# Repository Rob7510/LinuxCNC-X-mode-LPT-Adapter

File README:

# LinuxCNC signal adapter for a parallel port operating in X-mode.
**Version 153-01C**  work in progress

Many PC printer port cards can be operated in 'X' mode in **LinuxCNC**.
In X-mode the card provides 9 input ports (Pin 1, Pin 10-17) and 8 output ports (Pin 2 - Pin 9). This is usually sufficient for a small CNC. I do not know if other software than LinuxCNC can set a Printer port card in X-mode.

I do not know a commercial version of an X-mode LPT breakout board, but they are easy to build using a commercially produced dual layer PCB. This is the X-mode adapter design that I use for my CNC's running LinuxCNC.
The hardware is designed in Eagle; the .sch and .brd files are included, as well
as the Gerber files for manufacturing. The board size is kept to 10 x 10 cm to keep the manufacturing costs low (with Far-East PCB services).
The **CERN-OHL-P V2** license applies, which means that you are free to copy the design, modify it and
sell the result.

**Design features:**

  * The breakout board Input and Output ports are electrically separated from the PC using fast optical couplers. The PC side of the circuit is powered via a small 5V DC/DC converter.
  * The board can be directly plugged into the PC printer connector, or connected via a standard 26 wire ribbon cable with a printer connector on the other end. The 26 pin connector can also be used to plug in a signal monitor.
  * The Inputs for Pins 10 through 17 support a wide range of input signals (<u>+</u> 30V). The Pin 1 Input is fully isolated from the whole adapter, and can handle up to 300V AC or DC, for instance to check presence of the mains or driver voltage.

**Inputs:**

**Pin 1** requires one or two series resistors (for DC) or capacitors (for AC) so that the effctive current through the bipolar optocoupler (PC814) is 4 - 6 mA:

* For standard 5V signals user 680 Ohm series resistance. For voltages over 100V use two components in series.
* For DC voltages make sure the power dissipation in the resistor(s) does not exceed their rating.
* For mains voltage use 2 x xxxnF for 127V and 2 x xxxnF for 230V. Each capacitor should preferably be rated for 400V.
* The P1 LED lights up when it detects the incoming signal.

**Pins 10 - 17** are set to about 0V (False) for an input between -30 and + 0.5 V, and to 5V (True) for an input between 1.5 an 30V. The input lines are filtered to suppress high frequency (~ 10 KHz) pulses. The 10 pin ribbon connector is an alternative input for Pin 10 - 17, and provides ground and 5V to supply a remote input panel.

**Outputs:**

**Pins 2 - 9 **drive 5V signals with a current up to 10 mA. The 10 pin ribbon connector is an alternative output, and provides ground and 5V to supply remote distribution panels.

**Power supply:** To be updated

**Software:** To be updated

**Assembly:**

The X-mode adapter 153-01C is designed with through hole components to facilitate home assembly. The component list (BOM) gives the details.
The small capacitors (with values between 10 and 100 nF) are required to suppress RF disturbance.
The antiparallel diode next to the power connector will prevent damage in case the 5V is connected with the wrong polarity.
Is no electric separation from the PC is required, the 5V DC/DC converter can be replaced by two wires, and a USB power cable can be connected to a USB port on the PC.

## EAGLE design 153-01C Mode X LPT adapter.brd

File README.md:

# LinuxCNC signal adapter for a parallel port operating in X-mode.
**Version 153-01C**

Many PC printer port option boards can be operated in 'X' mode in **LinuxCNC**, by setting this mode in the 'loadrt hal_parport' command.
In X-mode the 25-pin I/O connector provides 9 input ports (Pin 1, Pin 10-17) and 8 output ports (Pin 2 - Pin 9). This is usually sufficient for a small CNC. (I do not know if other software than LinuxCNC can set a Printer port card in X-mode).

The signal breakout for an X-mode adapter can be home built with a low cost dual layer PCB, with full electric isolation from the connected PC. This document provides the Eagle design and the Gerber manufacturing files for such a Breakout Board (BoB). The board size is kept to 10 x 10 cm to keep the manufacturing costs low (with Far-East PCB services). The **CERN-OHL-P V2** OpenHardware license applies, hence you are free to copy the design, modify it and sell/use the result.

**Design:**

  * The BoB input and output ports are electrically separated from the PC using optical couplers. The PC side of the circuit is powered via a small 5V isolated DC/DC converter. Te board uses approximately 150 mA, and can be powered with an old USB-A power adapter.
  * The board can be directly plugged into a 25 pin PC printer port, or connected via a standard 26 wire ribbon cable with a printer port connector on the other end. The 26 pin connector can also be used to plug in a signal monitor.
  * The Inputs for Pins 10 through 17 support a wide range of input signals (<u>+</u> 30V). The Pin 1 Input is fully isolated from the whole board, and can handle up to 300V AC or DC signals, for instance to check presence of the mains voltage or Power supply output.

**Inputs:**

**Pin 1** requires one or two series resistors (for DC) or capacitors (for AC) so that the current through the bipolar optocoupler (PC814) is in the range of 4 - 10 mA:
* For standard 5V signals use a 680 Ohm resistor. For voltages over 100V use two components in series.
* For DC voltages make sure the power dissipation in the resistor(s) does not exceed their rating.
* For 230V mains voltage use 2 x 150nF (400V) in series. To keep high voltages away from the board, mount the capacitors or resistors at the source, and fill the two onboard slots with jumpers.
* The P1 LED lights up when it detects a valid signal.

**Pins 10 - 17** are set to about 0V (False) for an input between -30 and + 0.5 V, and to 5V (True) for an input between 1.5 an 30V. These inputs suppress high frequency (>5KHz) pulses. The 10 pin ribbon connector connects Pin 10 - 17, as well as GND and 5V to a remote input panel.

**Outputs:**

**Pins 2 - 9 ** drive 5V signals with a current up to 35 mA. The fast optical couplers (6N137) can handle pulses as short as 2 microseconds. The 10 pin ribbon connector is for connection to a remote breakout panel. All outputs (typically used for stepper signals) can be collectively turned off with a logic input signal.

**Power supply:**

The USB connector on the BoB should be connected to an separate 5V USB power supply to maintain electric isolation from the PC. The onboard 2-pin 5V connector can be used to supply other 5V hardware like relay boards. If PC isolation is not needed, the BoB can be connected to one of the PC USB plugs, and the DC/DC converter can be replaced by two wires.

**Software:** XPtest-0.hal and xptest-0.xml provide a display of the X-mode adapter I/O ports and check / set their status. The test assumes that the BoB connects to the first printer port that the PC discovers.

**Assembly:**

The X-mode adapter 153-01C uses through-hole components to facilitate home assembly. The component list (BOM) has the details.
The small capacitors (useful values between 10 and 100 nF) are required to suppress RF disturbance.
The antiparallel diode next to the power connector will prevent damage in case the 5V is connected with the wrong polarity (I hate replacing dead chips).

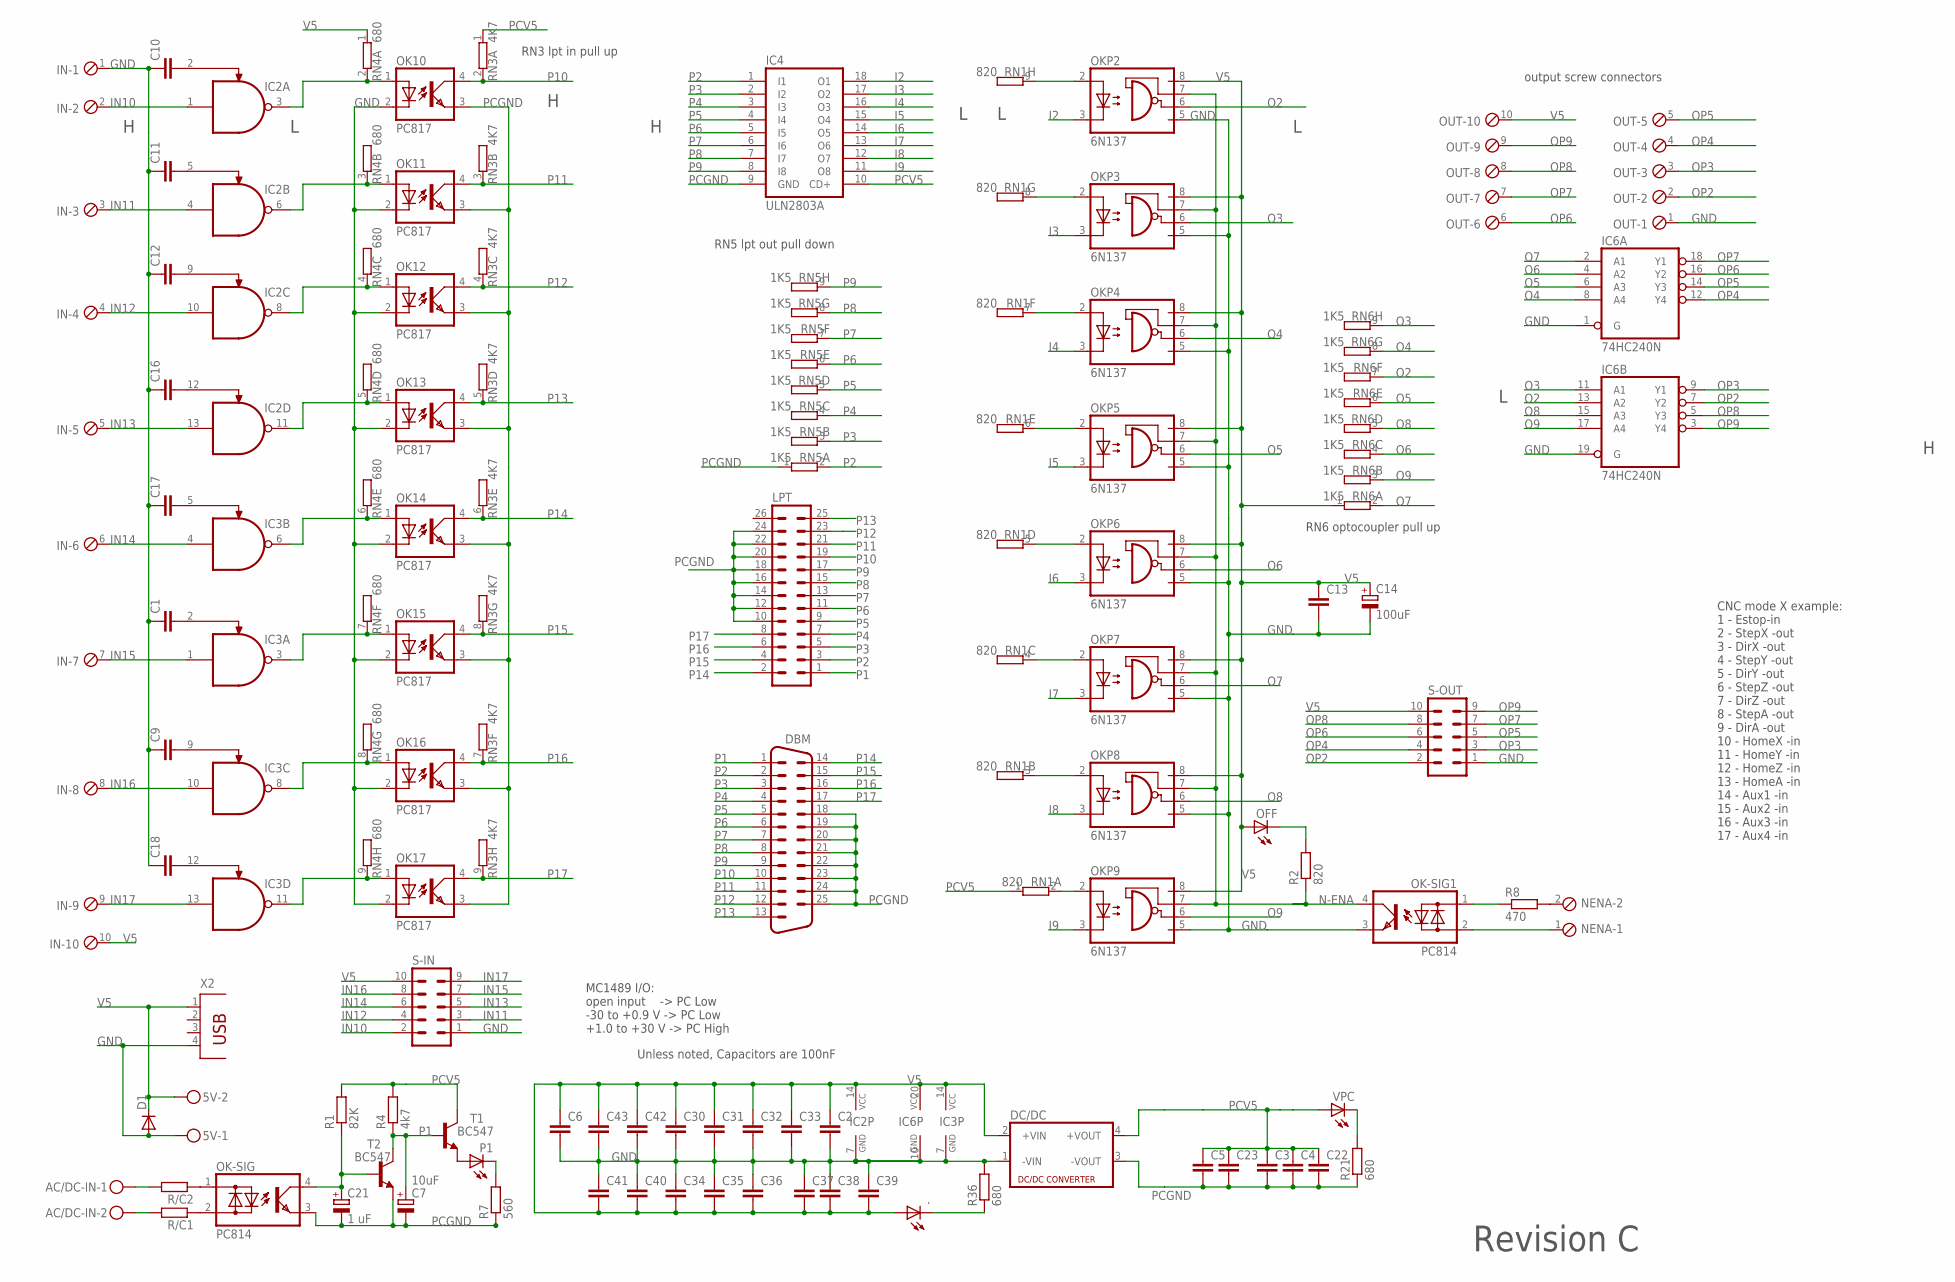
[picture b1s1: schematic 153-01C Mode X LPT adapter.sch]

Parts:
5V: MKDSN1,5/2-5,08
.: LED3MM
AC/DC-IN: MKDSN1,5/2-5,08
C1, C2, C3, C4, C5, C6, C9, C10, C11, C12, C13, C16, C17, C18, C22, C23, C30, C31, C32, C33, C34, C35, C36, C37, C38, C39, C40, C41, C42, C43: C-EU025-024X044; C025-024X044
C7: 10uF; E5-6
C14: 100uF; E3,5-8
C21: 1 uF; E2,5-6
D1: 1N4148DO35-10; DO35-10
DBM: M25HP
DC/DC: VA-1205S; 4SIL
IC2, IC3: MC1489DIP; DIL14
IC4: ULN2803A; DIL18
IC6: 74HC240N; DIL20
IN: MPT10; 10POL254
LPT: ML26
NENA: MPT2; 2POL254
OFF: LED3MM
OK10, OK11, OK12, OK13, OK14, OK15, OK16, OK17: PC817; DIL04
OK-SIG, OK-SIG1: PC814; DIL04
OKP2, OKP3, OKP4, OKP5, OKP6, OKP7, OKP8, OKP9: 6N137; DIL08
OUT: MPT10; 10POL254
P1: LED3MM
R1: 82K; 0207/10
R2: 820; 0207/10
R4: 4k7; 0207/10
R7: 560; 0207/10
R8: 470; 0207/10
R21, R36: 680; 0207/10
R/C1, R/C2: R-EU_0309/10; 0309/10
RN1: 820; SIL9
RN3: 4K7; SIL9
RN4: 680; SIL9
RN5, RN6: 1K5; SIL9
S-IN: ML10
S-OUT: ML10
T1, T2: BC547; TO92
VPC: LED3MM
X2: PN87520

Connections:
GND: 5V.1, C1.1, C2.2, C6.2, C9.1, C10.1, C11.1, C12.1, C13.2, C14.-, C16.1, C17.1, C18.1, C30.2, C31.2, C32.2, C33.2, C34.1, C35.1, C36.1, C37.1, C38.1, C39.1, C40.1, C41.1, C42.2, C43.2, D1.A, DC/DC.1 (-VIN), IC2.7 (GND), IC3.7 (GND), IC6.1 (G), IC6.10 (GND), IC6.19 (G), IN.1, OK10.2 (C), OK11.2 (C), OK12.2 (C), OK13.2 (C), OK14.2 (C), OK15.2 (C), OK16.2 (C), OK17.2 (C), OK-SIG1.3 (E), OKP2.5 (GND), OKP3.5 (GND), OKP4.5 (GND), OKP5.5 (GND), OKP6.5 (GND), OKP7.5 (GND), OKP8.5 (GND), OKP9.5 (GND), OUT.1, R36.2, S-IN.1, S-OUT.1, X2.4
I2: IC4.18 (O1), OKP2.3 (C)
I3: IC4.17 (O2), OKP3.3 (C)
I4: IC4.16 (O3), OKP4.3 (C)
I5: IC4.15 (O4), OKP5.3 (C)
I6: IC4.14 (O5), OKP6.3 (C)
I7: IC4.13 (O6), OKP7.3 (C)
I8: IC4.12 (O7), OKP8.3 (C)
I9: IC4.11 (O8), OKP9.3 (C)
IN10: IC2.1 (I0), IN.2, S-IN.2
IN11: IC2.4 (I0), IN.3, S-IN.3
IN12: IC2.10 (I0), IN.4, S-IN.4
IN13: IC2.13 (I0), IN.5, S-IN.5
IN14: IC3.4 (I0), IN.6, S-IN.6
IN15: IC3.1 (I0), IN.7, S-IN.7
IN16: IC3.10 (I0), IN.8, S-IN.8
IN17: IC3.13 (I0), IN.9, S-IN.9
unnamed: OKP6.2 (A), RN1.5 (2)
unnamed: OKP9.2 (A), RN1.2
unnamed: C10.2, IC2.2 (I1)
unnamed: R21.2, VPC.K (C)
unnamed: C17.2, IC3.5 (I1)
unnamed: OFF.K (C), R2.2
unnamed: IC2.6 (O), OK11.1 (A), RN4.3 (2)
unnamed: IC2.8 (O), OK12.1 (A), RN4.4 (2)
unnamed: C1.2, IC3.2 (I1)
unnamed: C9.2, IC3.9 (I1)
unnamed: C18.2, IC3.12 (I1)
unnamed: IC2.3 (O), OK10.1 (A), RN4.2
unnamed: IC2.11 (O), OK13.1 (A), RN4.5 (2)
unnamed: IC3.6 (O), OK14.1 (A), RN4.6 (2)
unnamed: IC3.3 (O), OK15.1 (A), RN4.7 (2)
unnamed: IC3.8 (O), OK16.1 (A), RN4.8 (2)
unnamed: OK-SIG.1 (AC1), R/C2.1
unnamed: OK-SIG.2 (AC2), R/C1.1
unnamed: IC3.11 (O), OK17.1 (A), RN4.9 (2)
unnamed: AC/DC-IN.2, R/C1.2
unnamed: AC/DC-IN.1, R/C2.2
unnamed: OKP7.2 (A), RN1.4 (2)
unnamed: OKP8.2 (A), RN1.3 (2)
unnamed: C21.+, OK-SIG.4 (C), R1.1, T2.2 (B)
unnamed: ..K (C), R36.1
unnamed: C11.2, IC2.5 (I1)
unnamed: C12.2, IC2.9 (I1)
unnamed: C16.2, IC2.12 (I1)
unnamed: OKP5.2 (A), RN1.6 (2)
unnamed: OKP4.2 (A), RN1.7 (2)
unnamed: OK-SIG1.1 (AC1), R8.1
unnamed: OKP3.2 (A), RN1.8 (2)
unnamed: OKP2.2 (A), RN1.9 (2)
unnamed: P1.K (C), R7.2
unnamed: P1.A, T1.1 (E)
unnamed: NENA.2, R8.2
unnamed: NENA.1, OK-SIG1.2 (AC2)
N-ENA: OK-SIG1.4 (C), OKP2.7 (VE), OKP3.7 (VE), OKP4.7 (VE), OKP5.7 (VE), OKP6.7 (VE), OKP7.7 (VE), OKP8.7 (VE), OKP9.7 (VE), R2.1
O2: IC6.13 (A2), OKP2.6 (VO), RN6.7 (2)
O3: IC6.11 (A1), OKP3.6 (VO), RN6.9 (2)
O4: IC6.8 (A4), OKP4.6 (VO), RN6.8 (2)
O5: IC6.6 (A3), OKP5.6 (VO), RN6.6 (2)
O6: IC6.4 (A2), OKP6.6 (VO), RN6.4 (2)
O7: IC6.2 (A1), OKP7.6 (VO), RN6.2
O8: IC6.15 (A3), OKP8.6 (VO), RN6.5 (2)
O9: IC6.17 (A4), OKP9.6 (VO), RN6.3 (2)
OP2: IC6.7 (Y2), OUT.2, S-OUT.2
OP3: IC6.9 (Y1), OUT.3, S-OUT.3
OP4: IC6.12 (Y4), OUT.4, S-OUT.4
OP5: IC6.14 (Y3), OUT.5, S-OUT.5
OP6: IC6.16 (Y2), OUT.6, S-OUT.6
OP7: IC6.18 (Y1), OUT.7, S-OUT.7
OP8: IC6.5 (Y3), OUT.8, S-OUT.8
OP9: IC6.3 (Y4), OUT.9, S-OUT.9
P1: C7.+, DBM.1, LPT.1, R4.1, T1.2 (B), T2.3 (C)
P2: DBM.2, IC4.1 (I1), LPT.3, RN5.2
P3: DBM.3, IC4.2 (I2), LPT.5, RN5.3 (2)
P4: DBM.4, IC4.3 (I3), LPT.7, RN5.4 (2)
P5: DBM.5, IC4.4 (I4), LPT.9, RN5.5 (2)
P6: DBM.6, IC4.5 (I5), LPT.11, RN5.6 (2)
P7: DBM.7, IC4.6 (I6), LPT.13, RN5.7 (2)
P8: DBM.8, IC4.7 (I7), LPT.15, RN5.8 (2)
P9: DBM.9, IC4.8 (I8), LPT.17, RN5.9 (2)
P10: DBM.10, LPT.19, OK10.4 (COL), RN3.2
P11: DBM.11, LPT.21, OK11.4 (COL), RN3.3 (2)
P12: DBM.12, LPT.23, OK12.4 (COL), RN3.4 (2)
P13: DBM.13, LPT.25, OK13.4 (COL), RN3.5 (2)
P14: DBM.14, LPT.2, OK14.4 (COL), RN3.6 (2)
P15: DBM.15, LPT.4, OK15.4 (COL), RN3.8 (2)
P16: DBM.16, LPT.6, OK16.4 (COL), RN3.7 (2)
P17: DBM.17, LPT.8, OK17.4 (COL), RN3.9 (2)
PCGND: C3.2, C4.2, C5.2, C7.-, C21.-, C22.2, C23.2, DBM.18, DBM.19, DBM.20, DBM.21, DBM.22, DBM.23, DBM.24, DBM.25, DC/DC.3 (-VOUT), IC4.9 (GND), LPT.10, LPT.12, LPT.14, LPT.16, LPT.18, LPT.20, LPT.22, LPT.24, OK10.3 (EMIT), OK11.3 (EMIT), OK12.3 (EMIT), OK13.3 (EMIT), OK14.3 (EMIT), OK15.3 (EMIT), OK16.3 (EMIT), OK17.3 (EMIT), OK-SIG.3 (E), R7.1, R21.1, RN5.1, T2.1 (E)
PCV5: C3.1, C4.1, C5.1, C22.1, C23.1, DC/DC.4 (+VOUT), IC4.10 (CD+), R1.2, R4.2, RN1.1, RN3.1, T1.3 (C), VPC.A
V5: 5V.2, ..A, C2.1, C6.1, C13.1, C14.+, C30.1, C31.1, C32.1, C33.1, C34.2, C35.2, C36.2, C37.2, C38.2, C39.2, C40.2, C41.2, C42.1, C43.1, D1.C, DC/DC.2 (+VIN), IC2.14 (VCC), IC3.14 (VCC), IC6.20 (VCC), IN.10, OFF.A, OKP2.8 (VCC), OKP3.8 (VCC), OKP4.8 (VCC), OKP5.8 (VCC), OKP6.8 (VCC), OKP7.8 (VCC), OKP8.8 (VCC), OKP9.8 (VCC), OUT.10, RN4.1, RN6.1, S-IN.10, S-OUT.10, X2.1

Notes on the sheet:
CNC mode X example: 1 - Estop-in 2 - StepX -out 3 - DirX -out 4 - StepY -out 5 - DirY -out 6 - StepZ -out 7 - DirZ -out 8 - StepA -out 9 - DirA -out 10 - HomeX -in 11 - HomeY -in 12 - HomeZ -in 13 - HomeA -in 14 - Aux1 -in 15 - Aux2 -in 16 - Aux3 -in 17 - Aux4 -in
MC1489 I/O: open input -> PC Low -30 to +0.9 V -> PC Low +1.0 to +30 V -> PC High
RN5 lpt out pull down
RN3 lpt in pull up
RN6 optocoupler pull up
output screw connectors
Unless noted, Capacitors are 100nF
Revision C

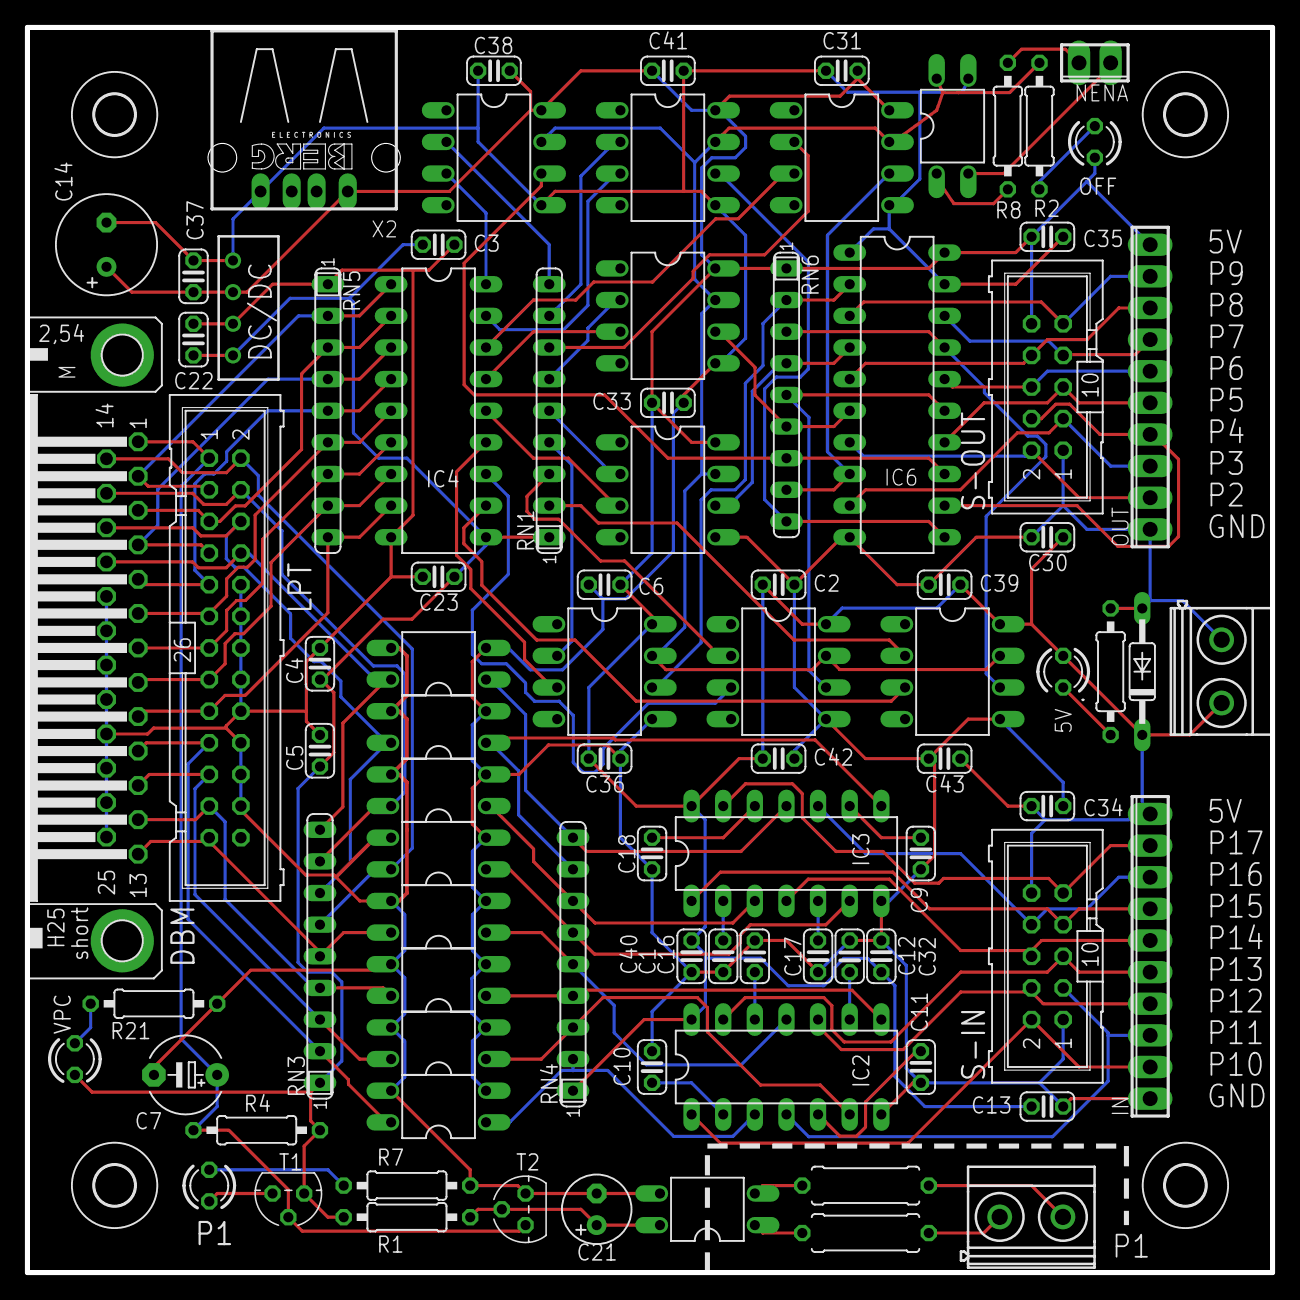
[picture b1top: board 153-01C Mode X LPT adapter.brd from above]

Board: 2 copper layers, 100.0 x 100.0 mm, 91 parts (0 on the bottom side), 91 nets.

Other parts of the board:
U$1, U$2, U$3, U$4: 3,2

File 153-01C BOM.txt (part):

Stückliste exportiert aus /home/robert/Project_data/Projects/153 LinuxCNC adapters/153-01C Mode X LPT adapter.sch am 03/07/2024 21:08

Part     Value     Device          Package         Description                           MF MPN          OC_FARNELL OC_NEWARK
.                  LED3MM          LED3MM          LED                                                                       
5V                 MKDSN1,5/2-5,08 MKDSN1,5/2-5,08 MKDSN 1,5/ 2-5,08 Printklemme                                             
AC/DC-IN           MKDSN1,5/2-5,08 MKDSN1,5/2-5,08 MKDSN 1,5/ 2-5,08 Printklemme                                             
C1                 C-EU025-024X044 C025-024X044    CAPACITOR, European symbol                                                
C2                 C-EU025-024X044 C025-024X044    CAPACITOR, European symbol                                                
C3                 C-EU025-024X044 C025-024X044    CAPACITOR, European symbol                                                
C4                 C-EU025-024X044 C025-024X044    CAPACITOR, European symbol                                                
C5                 C-EU025-024X044 C025-024X044    CAPACITOR, European symbol                                                
C6                 C-EU025-024X044 C025-024X044    CAPACITOR, European symbol                                                
C7       10uF      CPOL-EUE5-6     E5-6            POLARIZED CAPACITOR, European symbol                                      
C9                 C-EU025-024X044 C025-024X044    CAPACITOR, European symbol                                                
C10                C-EU025-024X044 C025-024X044    CAPACITOR, European symbol                                                
C11                C-EU025-024X044 C025-024X044    CAPACITOR, European symbol                                                
C12                C-EU025-024X044 C025-024X044    CAPACITOR, European symbol                                                
C13                C-EU025-024X044 C025-024X044    CAPACITOR, European symbol                                                
C14      100uF     CPOL-EUE3.5-8   E3,5-8          POLARIZED CAPACITOR, European symbol                                      
C16                C-EU025-024X044 C025-024X044    CAPACITOR, European symbol                                                
C17                C-EU025-024X044 C025-024X044    CAPACITOR, European symbol                                                
C18                C-EU025-024X044 C025-024X044    CAPACITOR, European symbol                                                
C21      1 uF      CPOL-EUE2.5-6   E2,5-6          POLARIZED CAPACITOR, European symbol                                      
C22                C-EU025-024X044 C025-024X044    CAPACITOR, European symbol                                                
C23                C-EU025-024X044 C025-024X044    CAPACITOR, European symbol                                                
C30                C-EU025-024X044 C025-024X044    CAPACITOR, European symbol                                                
C31                C-EU025-024X044 C025-024X044    CAPACITOR, European symbol                                                
C32                C-EU025-024X044 C025-024X044    CAPACITOR, European symbol                                                
C33                C-EU025-024X044 C025-024X044    CAPACITOR, European symbol                                                
C34                C-EU025-024X044 C025-024X044    CAPACITOR, European symbol                                                
C35                C-EU025-024X044 C025-024X044    CAPACITOR, European symbol                                                
C36                C-EU025-024X044 C025-024X044    CAPACITOR, European symbol                                                
C37                C-EU025-024X044 C025-024X044    CAPACITOR, European symbol                                                
C38                C-EU025-024X044 C025-024X044    CAPACITOR, European symbol                                                
C39                C-EU025-024X044 C025-024X044    CAPACITOR, European symbol                                                
C40                C-EU025-024X044 C025-024X044    CAPACITOR, European symbol                                                
C41                C-EU025-024X044 C025-024X044    CAPACITOR, European symbol                                                
C42                C-EU025-024X044 C025-024X044    CAPACITOR, European symbol                                                
C43                C-EU025-024X044 C025-024X044    CAPACITOR, European symbol                                                
D1                 1N4148DO35-10   DO35-10         DIODE                                                                     
DBM                M25HP           M25HP           SUB-D                                                 unknown    unknown  
DC/DC              VA-1205S        4SIL            DC DC Converter Single Output, 1 Watt                 unknown    unknown  
IC2      MC1489DIP MC1489DIP       DIL14           MC1489 quad line receiver DIP14                                           
IC3      MC1489DIP MC1489DIP       DIL14           MC1489 quad line receiver DIP14                                           
IC4      ULN2803A  ULN2803A        DIL18           DRIVER ARRAY                                                              
IC6      74HC240N  74HC240N        DIL20           Octal BUFFER and LINE DRIVER, 3-state                                     
IN                 MPT10           10POL254        PHOENIX CONNECTOR                                     unknown    unknown  
LPT                ML26            ML26            HARTING                                               unknown    unknown  
NENA               MPT2            2POL254         PHOENIX CONNECTOR                                     unknown    unknown  
OFF                LED3MM          LED3MM          LED                                                                       
OK-SIG   PC814     PC814           DIL04           SHARP OPTO COUPLER                                    9707662    unknown  
OK-SIG1  PC814     PC814           DIL04           SHARP OPTO COUPLER                                    9707662    unknown  
OK10     PC817     PC817           DIL04           SHARP OPTO COUPLER                       PC817X4J000F 9707727    97K7059  
OK11     PC817     PC817           DIL04           SHARP OPTO COUPLER                       PC817X4J000F 9707727    97K7059  
OK12     PC817     PC817           DIL04           SHARP OPTO COUPLER                       PC817X4J000F 9707727    97K7059  
OK13     PC817     PC817           DIL04           SHARP OPTO COUPLER                       PC817X4J000F 9707727    97K7059  
OK14     PC817     PC817           DIL04           SHARP OPTO COUPLER                       PC817X4J000F 9707727    97K7059  
OK15     PC817     PC817           DIL04           SHARP OPTO COUPLER                       PC817X4J000F 9707727    97K7059  
OK16     PC817     PC817           DIL04           SHARP OPTO COUPLER                       PC817X4J000F 9707727    97K7059  
OK17     PC817     PC817           DIL04           SHARP OPTO COUPLER                       PC817X4J000F 9707727    97K7059  
OKP2     6N137     6N137           DIL08           MOTOROLA OPTO COUPLER                    6N137        1328376    52M1895  
OKP3     6N137     6N137           DIL08           MOTOROLA OPTO COUPLER                    6N137        1328376    52M1895  
OKP4     6N137     6N137           DIL08           MOTOROLA OPTO COUPLER                    6N137        1328376    52M1895  
OKP5     6N137     6N137           DIL08           MOTOROLA OPTO COUPLER                    6N137        1328376    52M1895  
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
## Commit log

2024-07-04 Got the initial list back Remove deleted files from repository
2024-07-04 New upload, removed the DSN file
2024-07-04 Update of text ofn the PCB top layer
2024-07-05 updated top silkscreen, created Eagle and Gerber directory
2024-07-05 Added the 2 direvctories
2024-07-05 Updated READ.me
2024-07-06 Renamed READ.me to README
2024-07-09 Updated readme, added test routine
2024-07-09 added tests...
2024-08-26 Upated README and images
2024-08-26 Updated images
2024-10-04 updated tests and brd image

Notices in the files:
153-01C Mode X LPT adapter.brd:
License: CERN-OHL-P V2
